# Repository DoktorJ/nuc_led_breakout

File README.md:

# nuc_led_breakout
Dual RGB LED breakout board for NUC 7/8/10

Author assumes no liability for any damage that may arise through your production, assembly, or use of this board,
whether to the board, to the NUC, or to anything (or anyone) else!

## License
The design and use of this board is licensed under the [Creative Commons Attribution-Sharealike 2.0 license](https://creativecommons.org/licenses/by-sa/2.0/)
(cc-by-sa-2.0) license.

## Intent
This board is for debugging the RGB headers on a NUC10. Attaches via a short Molex Picoblade 4p pigtail.
Dual RGB LEDs mount at each end for redundancy and visibility, with individual current limiting resistors for each element of each LED.
This board may not be suitable for use with the NUC enclosure assembled due to through-hole parts with exposed metal points; attempt this at your own risk.

## Connection
The NUC header consists of a 4-pin 1.25mm pitch connector; pin 1 is +3VSB, and with 2, 3, and 4 sinking red, green, and blue respectively.

## Parts selection
Since the NUC has a common +3V power source, this design takes the simplest adaptation of that and is made for a common anode RGB LED. Since pinouts may
vary by LED, be aware that the board is designed for this specific pinout:

    1. - Green
    2. - Blue
    3. + Common
    4. - Red
    
Be aware that some RGB LEDs reverse the pins for green and blue. If you use one of these LEDs the circuit will still technically work, but the
colors will be reversed (green<->blue and magenta<->yellow; red, cyan, and white will work correctly). An RGB LED with the anode at pins 1 or 4
will NOT work (and may or may not let the magic smoke out).

Beyond that, you will need to do the math for your LEDs and their resistors -- check the LED's datasheet. In most, the green and blue elements will
have a _Vf_ greater than 3V and thus technically will not need resistors; you can shunt them with bare wire, but a low-resistance (<10Ω) resistor
shouldn't affect brightness significantly while providing a bit of protection. The red element almost always has a _Vf_ *below* 3V, so calculate

> (3 - _Vf_) ÷ _If_  (remember, _If_ is in amps, so 20mA = 0.02A)

and round up to the nearest available value.

Note that the resistors are paired; R1 and R4 should have equivalent values (assuming the two RGB LEDs used are the same), as should R2/R5, and R3/R6.

Lastly, the connector is Molex p/n 0530470410 . For the most part, any 1.25mm pitch 4-pin header should work, but the Molex Picoblade jumpers
(e.g. 0151340400) fit the NUC header, so it makes sense to use the mating male header on the board barring availability issues.

## Usage

After assembling the board, take an appropriate Molex Picoblade pigtail and connect to your board. Note which side plugs into pin 1 (the end closest
to the "J1" identifier; appropriate "1" mark coming in a future release), it may help to mark the pin 1 connector on each end of the pigtail with a
permanent marker.

Flip your NUC over and take off its bottom plate. Now, depending on your NUC model, the RGB header will be in different places. Be aware the header
may be occupied if an external LED (e.g. ring on NUC 7) is connected, and would need to be disconnected. Find pin 1 of the header, and plug the
pigtail into the header.

Enjoy, and don't brick your NUC!

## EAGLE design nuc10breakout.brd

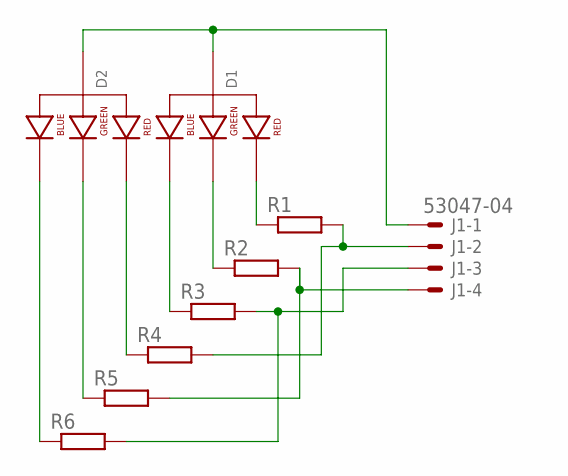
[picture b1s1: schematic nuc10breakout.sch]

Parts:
D1, D2: LED-RGB-CA-THRUDIFFUSE; LED-RGB-THRU
J1: 53047-04
R1, R2, R3, R4, R5, R6: R-EU_0204/5; 0204/5

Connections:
unnamed: J1.2, R1.2, R4.2
unnamed: J1.4, R2.2, R5.2
unnamed: J1.3, R3.2, R6.2
unnamed: D1.1 (RED_CATHODE), R1.1
unnamed: D1.3 (GREEN_CATHODE), R2.1
unnamed: D1.4 (BLUE_CATHODE), R3.1
unnamed: D1.2 (ANODE), D2.2 (ANODE), J1.1
unnamed: D2.1 (RED_CATHODE), R4.1
unnamed: D2.3 (GREEN_CATHODE), R5.1
unnamed: D2.4 (BLUE_CATHODE), R6.1

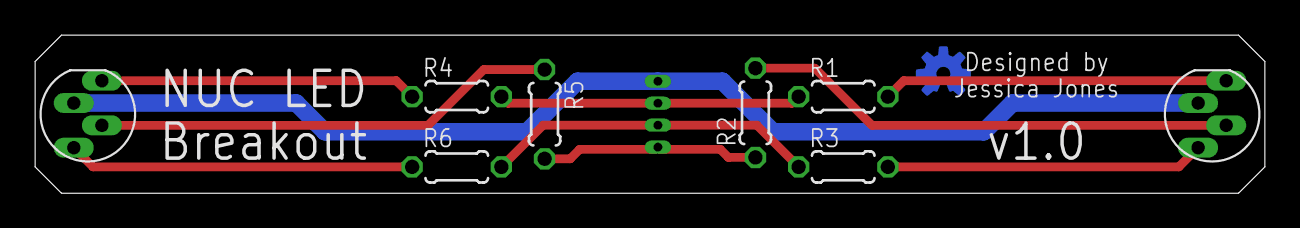
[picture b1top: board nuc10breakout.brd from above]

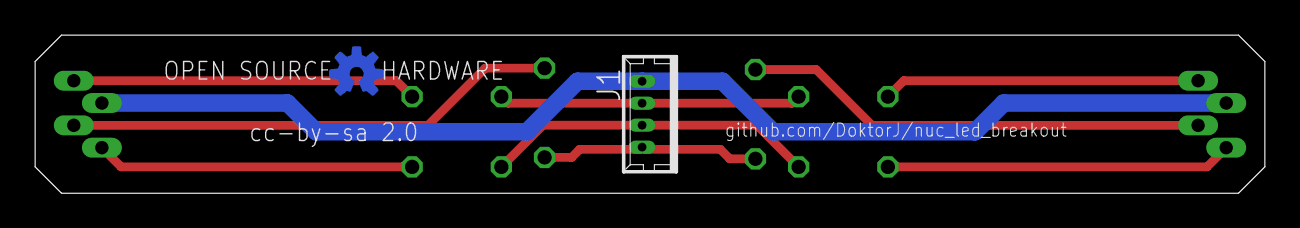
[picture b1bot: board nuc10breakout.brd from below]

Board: 2 copper layers, 70.0 x 9.0 mm, 10 parts (2 on the bottom side), 10 nets.

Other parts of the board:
U$1: OSHW-LOGO-S_COPPER

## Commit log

2020-08-19 Original EAGLE 7.4 files
    Initial commit, the original board/schematic in EAGLE format.

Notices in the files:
parts and their libraries:
SparkFun-LED: Licensing: Creative Commons ShareAlike 4.0 International - https://creativecommons.org/licenses/by-sa/4.0
